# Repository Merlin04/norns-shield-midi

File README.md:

# norns-shield-midi

norns shield variant with hardware MIDI in/out ([TRS minijack connectors](https://minimidi.world/)), based on the 210330 version of the original [norns shield](https://github.com/monome/norns-shield)

also:
- PCB files ported to kicad
- board outline cleaned up a bit (slightly smaller? probably won't matter)
- MIDI in works with Type-A or Type-B (circuit based on [LPZW auto-crossover MIDI input](https://github.com/kay-lpzw/LPZW_TRS_MIDI), same as shieldXL i think?)
- MIDI out has a switch to choose between Type-A and Type-B

## getting one

this design is currently untested but boards are on the way to me. once i get them, finish assembly, and test one, i'll (try to remember to) update this page. 

i'll have a few extra boards (with SMT components assembled), if you're interested in buying one from me for cost of parts+shipping feel free to reach out - discord username is same as github username, and i'm @m04 on lines

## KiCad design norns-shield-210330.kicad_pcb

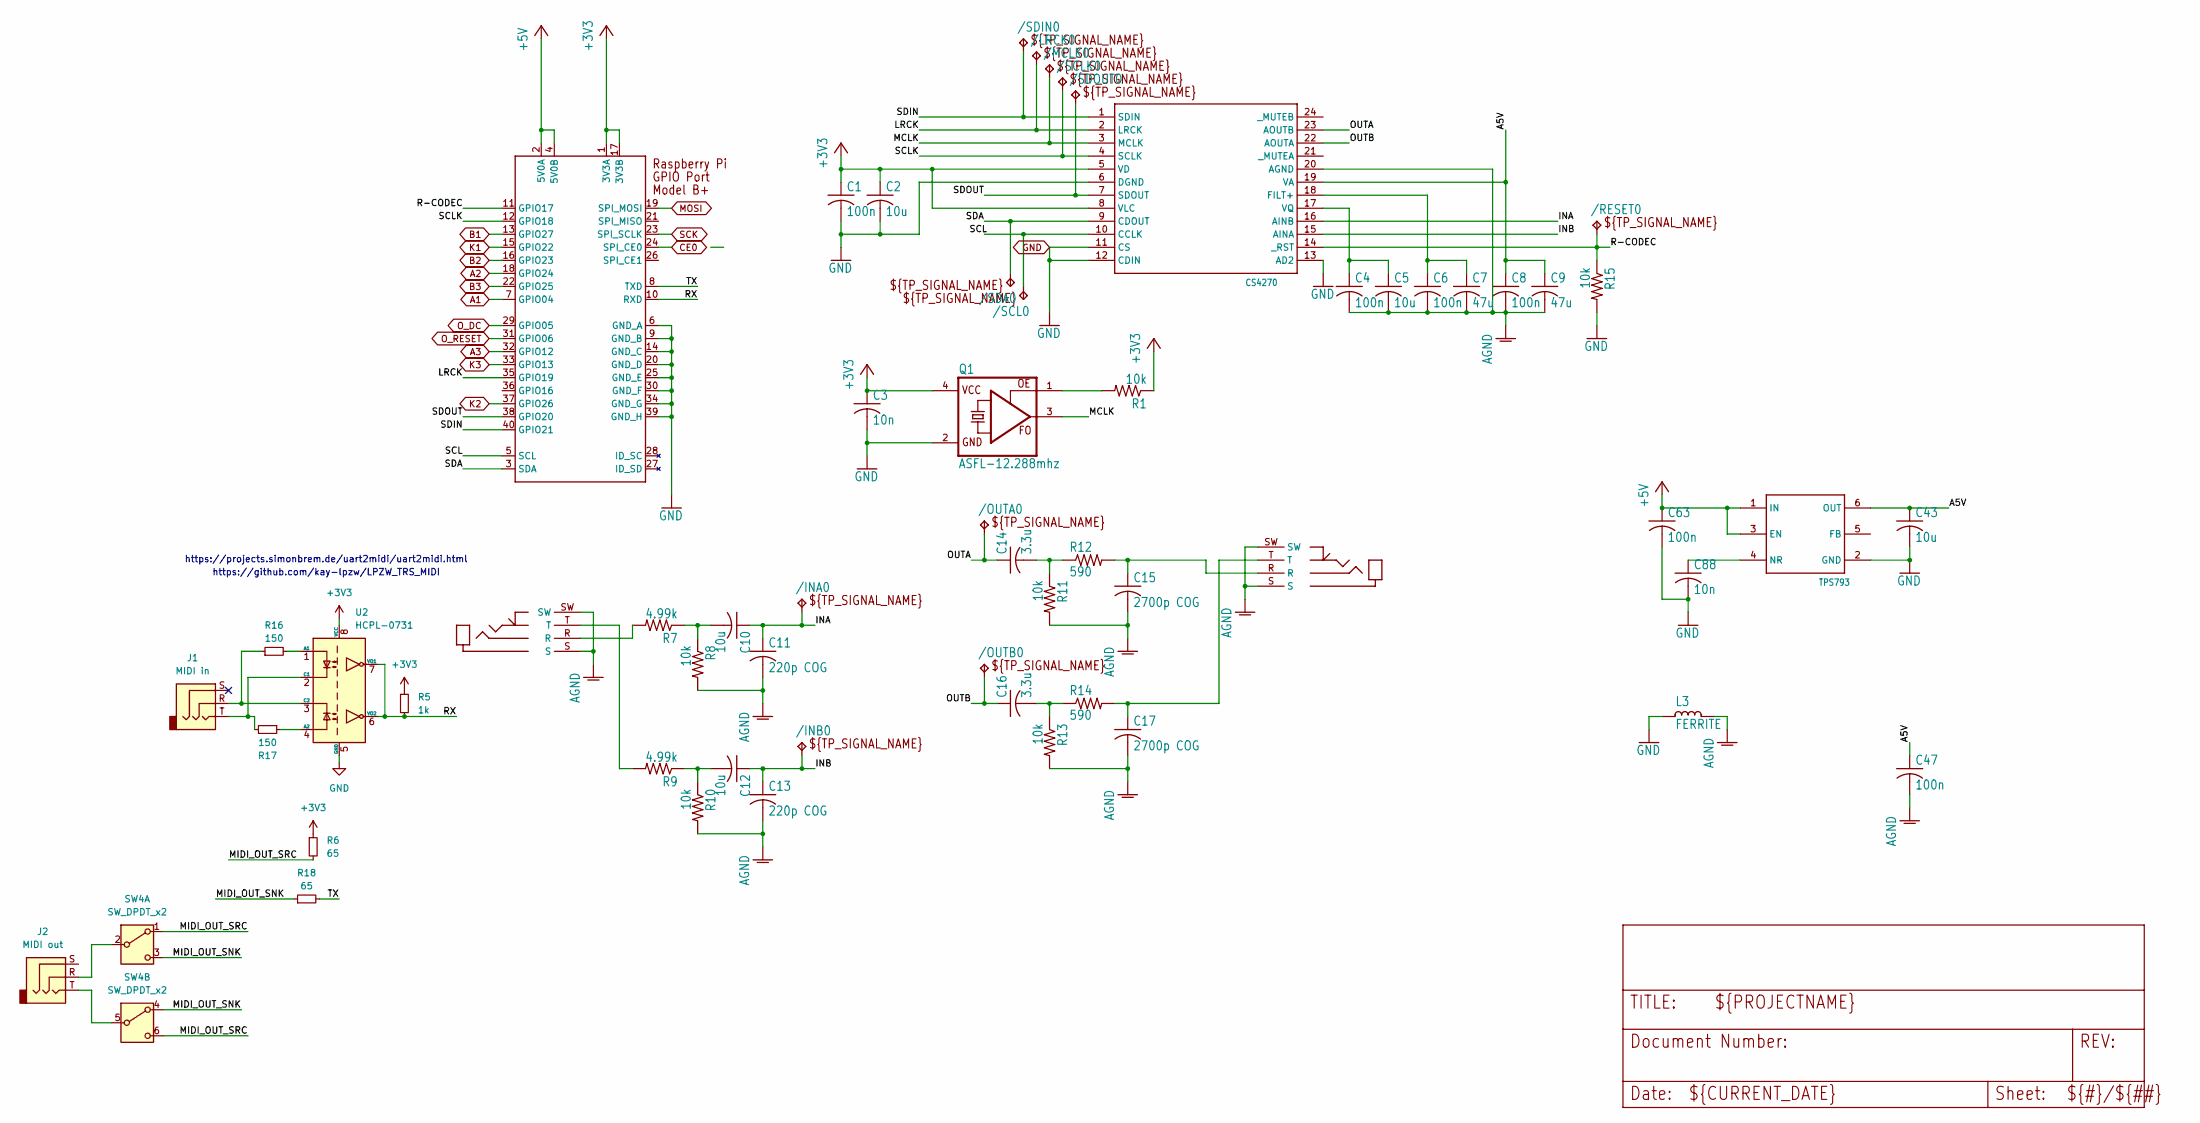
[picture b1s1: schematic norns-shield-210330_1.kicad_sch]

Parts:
/INA0: TPTP12R; TP12R
/INB0: TPTP12R; TP12R
/LRCK0: TPTP12R; TP12R
/MCLK0: TPTP12R; TP12R
/OUTA0: TPTP12R; TP12R
/OUTB0: TPTP12R; TP12R
/RESET0: TPTP12R; TP12R
/SCL0: TPTP12R; TP12R
/SCLK0: TPTP12R; TP12R
/SDA0: TPTP12R; TP12R
/SDIN0: TPTP12R; TP12R
/SDOUT0: TPTP12R; TP12R
C1, C4, C6, C8, C47, C63: 100n; C_0603_1608Metric
C2, C5, C10, C12, C43: 10u; C_0805_2012Metric
C3, C88: 10n; C_0603_1608Metric
C7, C9: 47u; C_1206_3216Metric
C11, C13: 220p COG; C_0603_1608Metric
C14, C16: 3.3u; C_0805_2012Metric
C15, C17: 2700p COG; C_0603_1608Metric
J1: MIDI in; JACK4832.2330
J2: MIDI out; JACK4832.2330
J-IN0: JACK-TRS-SW; JACK4832.2330
J-OUT0: JACK-TRS-SW; JACK4832.2330
L3: FERRITE; L_0805_2012Metric
Q1: ASFL-12.288mhz; ASF
R1, R8, R10, R11, R13, R15: 10k; R_0603_1608Metric
R5: 1k; R_0603_1608Metric
R6, R18: 65; R_0603_1608Metric
R7, R9: 4.99k; R_0603_1608Metric
R12, R14: 590; R_0603_1608Metric
R16, R17: 150; R_0603_1608Metric
SW4: SW_DPDT_x2; JS202011JAQN
U1: CS4270; TSSOP24
U2: HCPL-0731; SOIC-8_3.9x4.9mm_P1.27mm
U11: TPS793; SSOP6
X1: RASPI_BOARD_B+#_E3; RASPI_BOARD_B+_EDGES_3DRILL

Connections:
+3V3: C1.1, C2.1, C3.1, Q1.4 (VCC), R1.1, R5.1, R6.1, U1.5 (VD), U1.8 (VLC), U2.8 (VCC), X1.1 (3V3A), X1.17 (3V3B); also elsewhere on the board
+5V: C63.1, U11.1 (IN), U11.3 (EN), X1.2 (5V0A), X1.4 (5V0B)
/norns-shield-210330_1/A5V: C8.1, C9.1, C43.1, C47.1, U1.19 (VA), U11.6 (OUT)
/norns-shield-210330_1/INA: /INA0.TP, C10.1, C11.1, U1.16 (AINB)
/norns-shield-210330_1/INB: /INB0.TP, C12.1, C13.1, U1.15 (AINA)
/norns-shield-210330_1/LRCK: /LRCK0.TP, U1.2 (LRCK), X1.35 (GPIO19)
/norns-shield-210330_1/MCLK: /MCLK0.TP, Q1.3 (FO), U1.3 (MCLK)
/norns-shield-210330_1/MIDI_OUT_SNK: R18.1, SW4.3 (C), SW4.4 (A)
/norns-shield-210330_1/MIDI_OUT_SRC: R6.2, SW4.1 (A), SW4.6 (C)
/norns-shield-210330_1/OUTA: /OUTA0.TP, C14.1, U1.23 (AOUTB)
/norns-shield-210330_1/OUTB: /OUTB0.TP, C16.1, U1.22 (AOUTA)
/norns-shield-210330_1/R-CODEC: /RESET0.TP, R15.1, U1.14 (_RST), X1.11 (GPIO17)
/norns-shield-210330_1/RX: R5.2, U2.6 (VO2), U2.7 (VO1), X1.10 (RXD)
/norns-shield-210330_1/SCL: /SCL0.TP, U1.10 (CCLK), X1.5 (SCL)
/norns-shield-210330_1/SCLK: /SCLK0.TP, U1.4 (SCLK), X1.12 (GPIO18)
/norns-shield-210330_1/SDA: /SDA0.TP, U1.9 (CDOUT), X1.3 (SDA)
/norns-shield-210330_1/SDIN: /SDIN0.TP, U1.1 (SDIN), X1.40 (GPIO21)
/norns-shield-210330_1/SDOUT: /SDOUT0.TP, U1.7 (SDOUT), X1.38 (GPIO20)
/norns-shield-210330_1/TX: R18.2, X1.8 (TXD)
A1: X1.7 (GPIO04); also elsewhere on the board
A2: X1.18 (GPIO24); also elsewhere on the board
A3: X1.32 (GPIO12); also elsewhere on the board
AGND: C4.2, C5.2, C6.2, C7.2, C8.2, C9.2, C11.2, C13.2, C15.2, C17.2, C47.2, J-IN0.S, J-IN0.SW, J-OUT0.S, J-OUT0.SW, L3.1, R8.2, R10.2, R11.2, R13.2, U1.20 (AGND)
B1: X1.13 (GPIO27); also elsewhere on the board
B2: X1.16 (GPIO23); also elsewhere on the board
B3: X1.22 (GPIO25); also elsewhere on the board
CE0: X1.24 (SPI_CE0); also elsewhere on the board
GND: C1.2, C2.2, C3.2, C43.2, C63.2, C88.2, L3.2, Q1.2 (GND), R15.2, U1.6 (DGND), U1.11 (CS), U1.12 (CDIN), U1.13 (AD2), U2.5 (GND), U11.2 (GND), X1.6 (GND_A), X1.9 (GND_B), X1.14 (GND_C), X1.20 (GND_D), X1.25 (GND_E), X1.30 (GND_F), X1.34 (GND_G), X1.39 (GND_H); also elsewhere on the board
K1: X1.15 (GPIO22); also elsewhere on the board
K2: X1.37 (GPIO26); also elsewhere on the board
K3: X1.33 (GPIO13); also elsewhere on the board
MOSI: X1.19 (SPI_MOSI); also elsewhere on the board
unnamed: C10.2, R7.1, R8.1
unnamed: C12.2, R9.1, R10.1
unnamed: C14.2, R11.1, R12.1
unnamed: C15.1, J-OUT0.R, R12.2
unnamed: C16.2, R13.1, R14.1
unnamed: C17.1, J-OUT0.T, R14.2
unnamed: J-IN0.R, R7.2
unnamed: J-IN0.T, R9.2
unnamed: Q1.1 (OE), R1.2
unnamed: J2.R, SW4.2 (B)
unnamed: J2.T, SW4.5 (B)
unnamed: C6.1, C7.1, U1.18 (FILT+)
unnamed: C4.1, C5.1, U1.17 (VQ)
unnamed: R16.2, U2.1 (A1)
unnamed: R17.1, U2.4 (A2)
unnamed: J1.T, R17.2, U2.2 (C1)
unnamed: J1.R, R16.1, U2.3 (C2)
unnamed: C88.1, U11.4 (NR)
O_DC: X1.29 (GPIO05); also elsewhere on the board
O_RESET: X1.31 (GPIO06); also elsewhere on the board
SCK: X1.23 (SPI_SCLK); also elsewhere on the board

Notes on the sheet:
https://github.com/kay-lpzw/LPZW_TRS_MIDI
https://projects.simonbrem.de/uart2midi/uart2midi.html

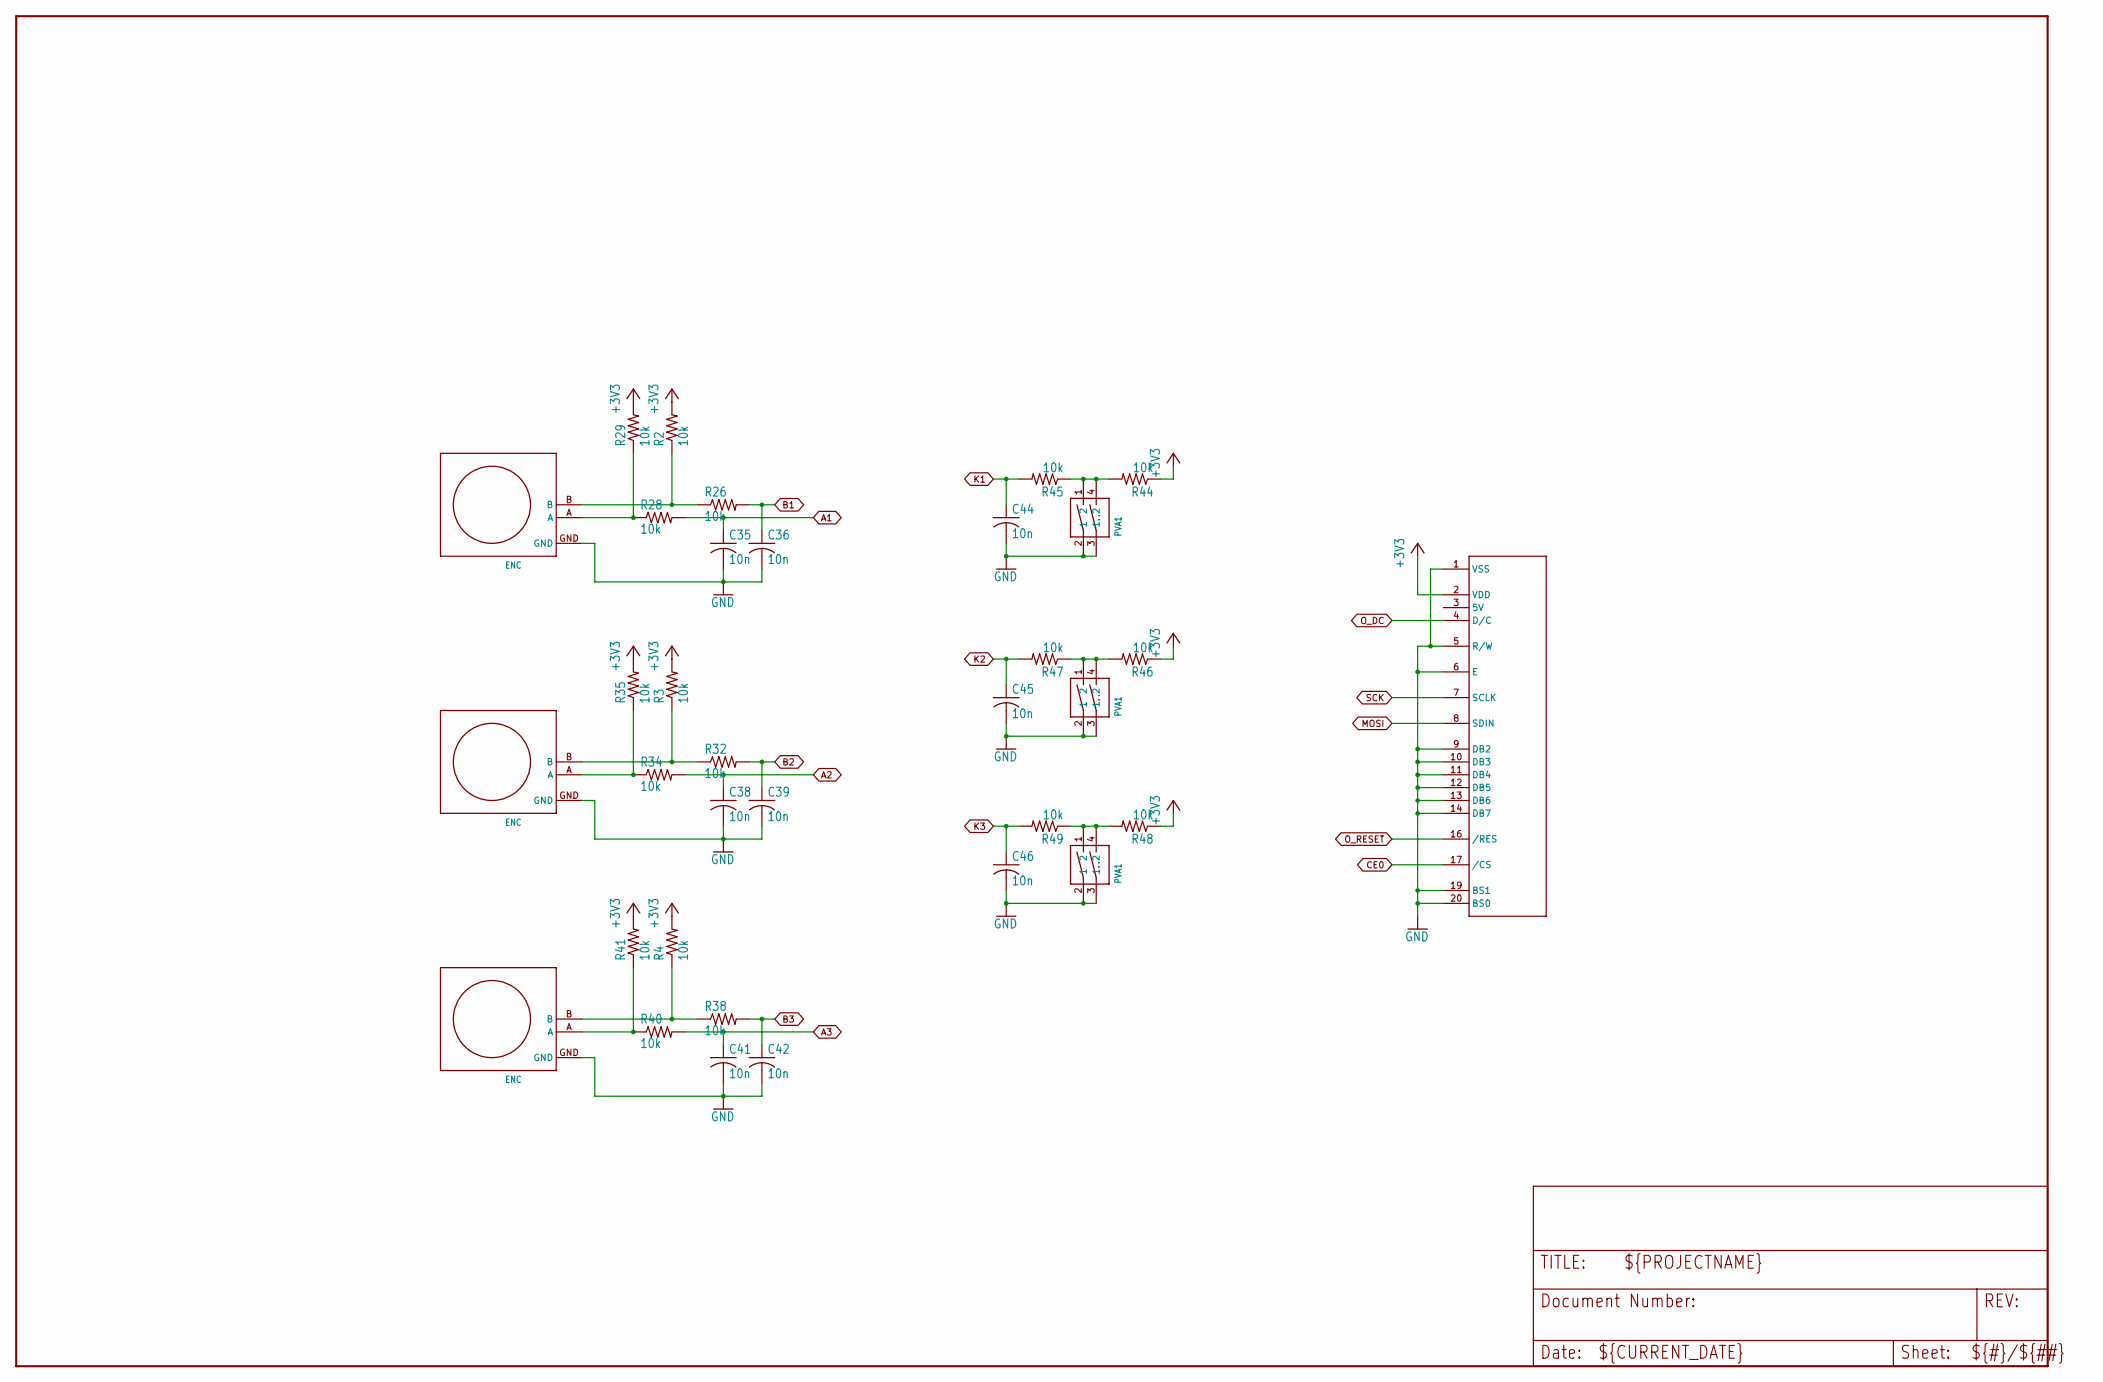
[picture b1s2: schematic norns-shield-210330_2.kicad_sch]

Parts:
C35, C36, C38, C39, C41, C42, C44, C45, C46: 10n; C_0603_1608Metric
E1, E2, E3: ENC; PEC11RN
R2, R3, R4, R26, R28, R29, R32, R34, R35, R38, R40, R41, R44, R45, R46, R47, R48, R49: 10k; R_0603_1608Metric
SW1, SW2, SW3: PVA1
U$1: OLED128X64; OLED-ALEPH

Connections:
+3V3: R2.2, R3.2, R4.2, R29.2, R35.2, R41.2, R44.1, R46.1, R48.1, U$1.2 (VDD); also elsewhere on the board
A1: C35.1, R28.2; also elsewhere on the board
A2: C38.1, R34.2; also elsewhere on the board
A3: C41.1, R40.2; also elsewhere on the board
B1: C36.1, R26.2; also elsewhere on the board
B2: C39.1, R32.2; also elsewhere on the board
B3: C42.1, R38.2; also elsewhere on the board
CE0: U$1.17 (/CS); also elsewhere on the board
GND: C35.2, C36.2, C38.2, C39.2, C41.2, C42.2, C44.2, C45.2, C46.2, E1.GND, E2.GND, E3.GND, SW1.2 (1), SW1.3 (1.), SW2.2 (1), SW2.3 (1.), SW3.2 (1), SW3.3 (1.), U$1.1 (VSS), U$1.5 (R/W), U$1.6 (E), U$1.9 (DB2), U$1.10 (DB3), U$1.11 (DB4), U$1.12 (DB5), U$1.13 (DB6), U$1.14 (DB7), U$1.19 (BS1), U$1.20 (BS0); also elsewhere on the board
K1: C44.1, R45.2; also elsewhere on the board
K2: C45.1, R47.2; also elsewhere on the board
K3: C46.1, R49.2; also elsewhere on the board
MOSI: U$1.8 (SDIN); also elsewhere on the board
unnamed: E1.A, R28.1, R29.1
unnamed: E1.B, R2.1, R26.1
unnamed: E2.A, R34.1, R35.1
unnamed: E2.B, R3.1, R32.1
unnamed: E3.A, R40.1, R41.1
unnamed: E3.B, R4.1, R38.1
unnamed: R44.2, R45.1, SW1.1 (2), SW1.4 (.2)
unnamed: R46.2, R47.1, SW2.1 (2), SW2.4 (.2)
unnamed: R48.2, R49.1, SW3.1 (2), SW3.4 (.2)
O_DC: U$1.4 (D/C); also elsewhere on the board
O_RESET: U$1.16 (/RES); also elsewhere on the board
SCK: U$1.7 (SCLK); also elsewhere on the board

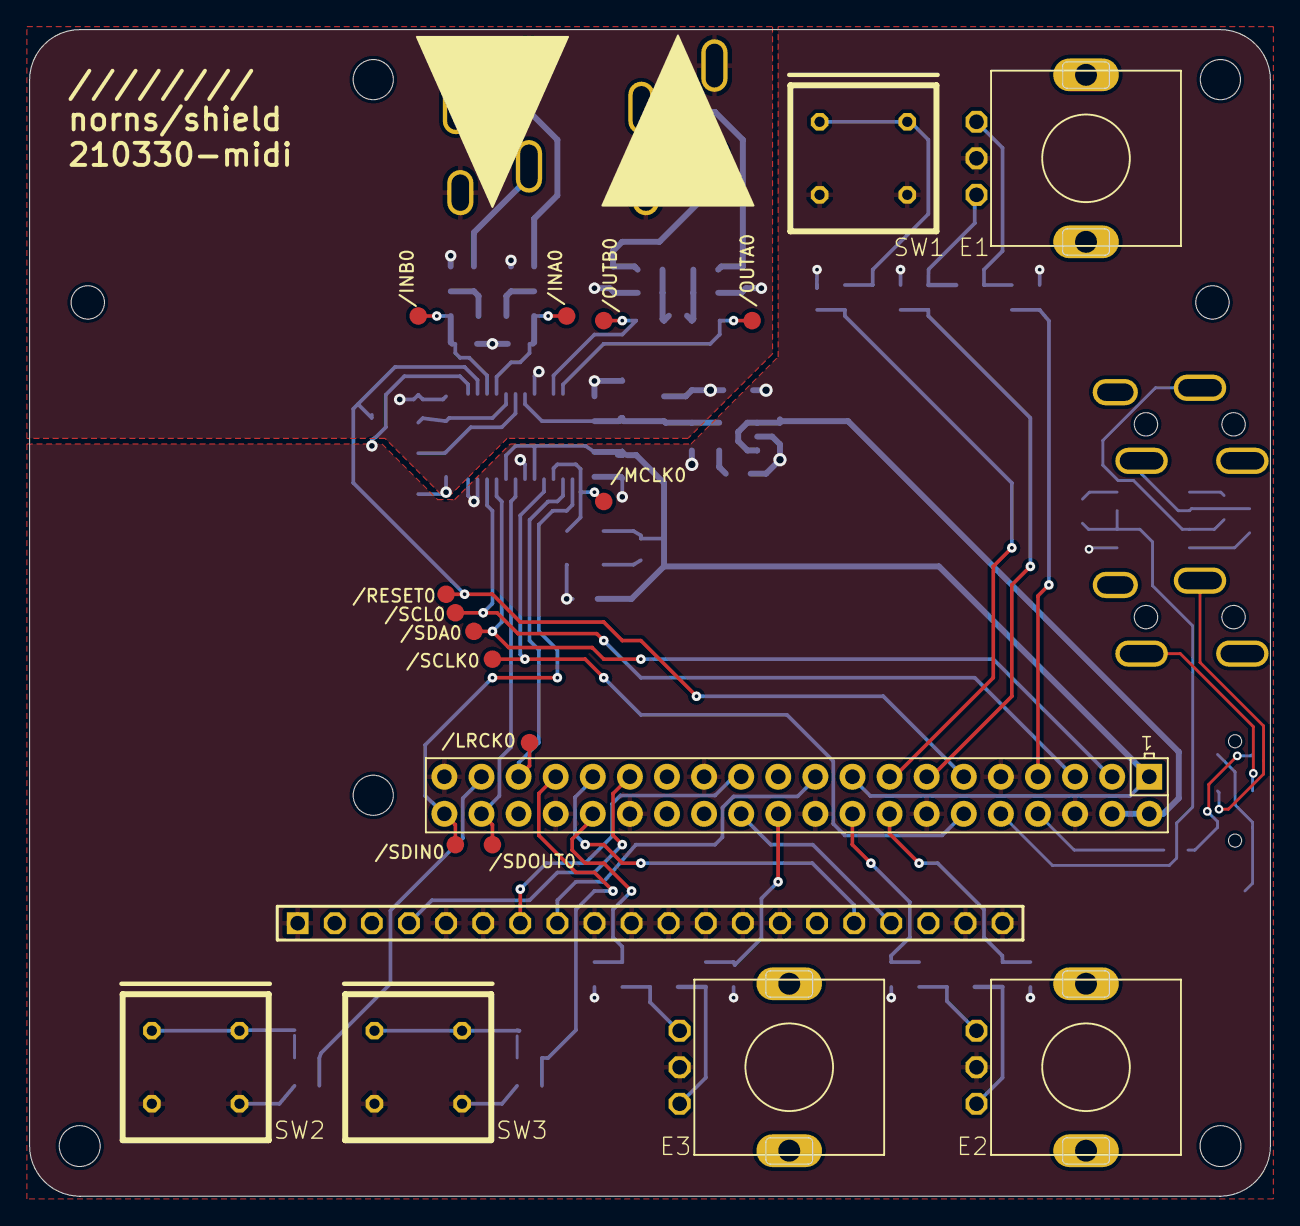
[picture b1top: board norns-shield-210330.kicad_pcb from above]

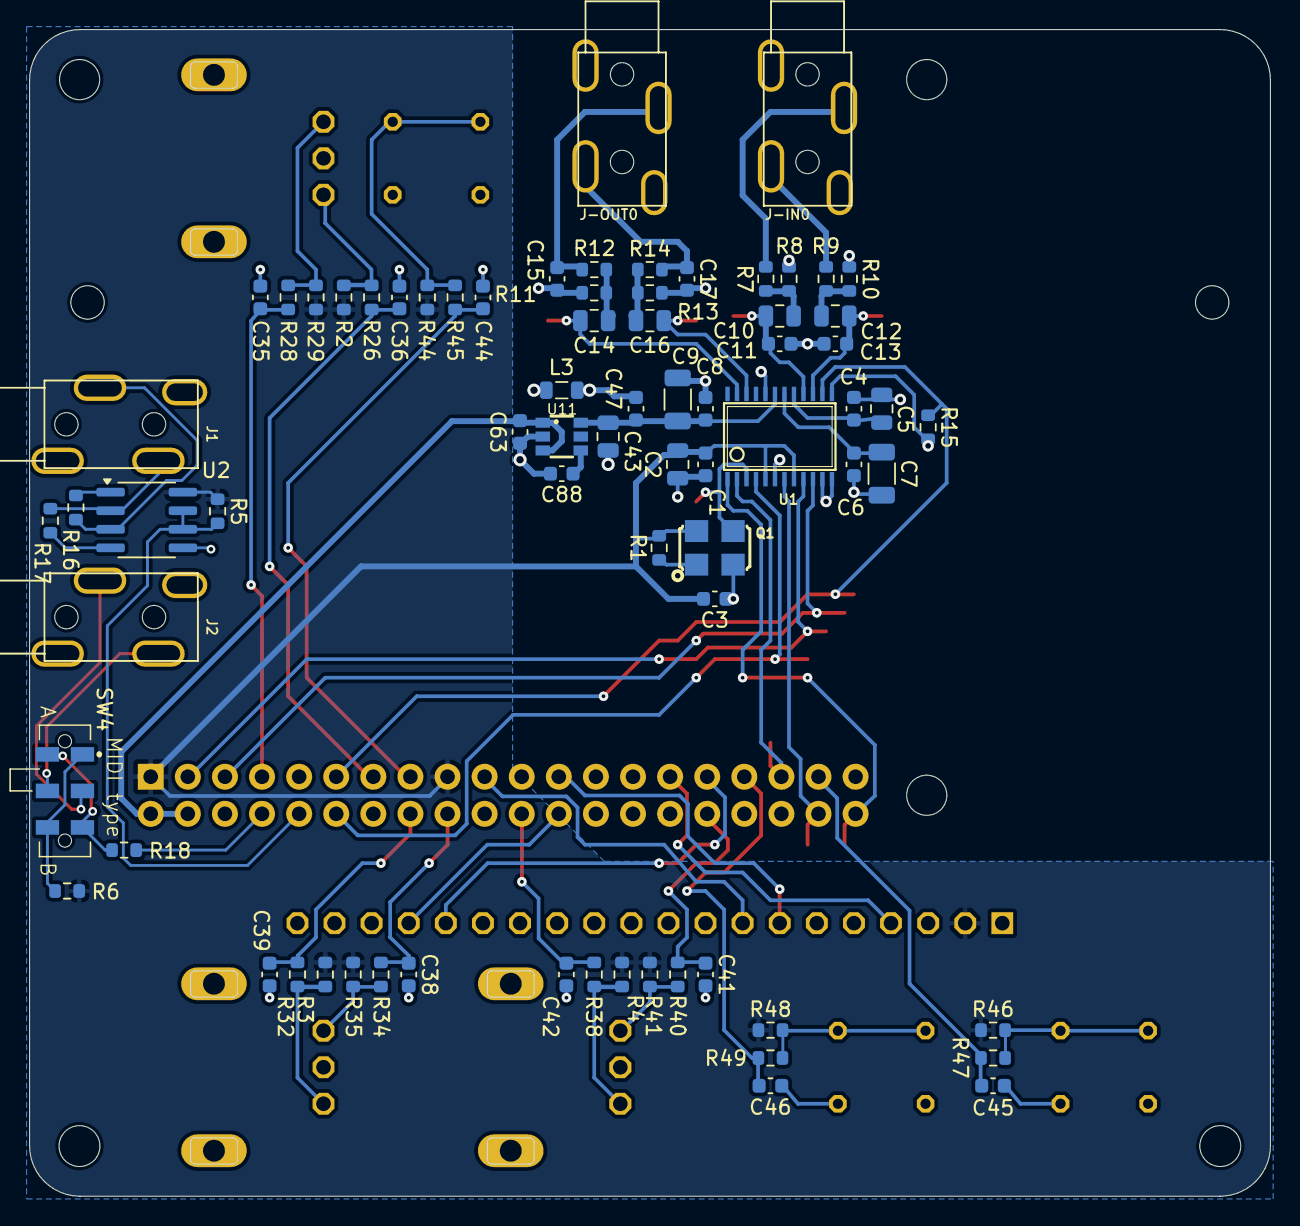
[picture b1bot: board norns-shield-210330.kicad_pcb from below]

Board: 2 copper layers, 85.0 x 79.9 mm, 95 parts (73 on the bottom side), 62 nets.

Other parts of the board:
@HOLE0, @HOLE1: (no value)

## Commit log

2025-01-01 Add files
2025-01-01 README
